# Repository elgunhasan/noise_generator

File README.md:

| Band | S-meter | μV |
| ------ | ------ |------ |
| 10 meter | 8 | 31 |
| 12 meter | 8 | 31 |
| 15 meter | 9 | 61 |
| 17 meter | 9 | 61 |
| 20 meter | 9+10 db | 190 |
| 30 meter | 9+20 db | 610 |
| 40 meter | 9+20 db | 610 |
| 80 meter | 9+20 db | 610 |
| 160 meter | 9+20 db | 610 |

You can change the resistor R1 with a potentiometer and find out at which value the strongest noise occurs.

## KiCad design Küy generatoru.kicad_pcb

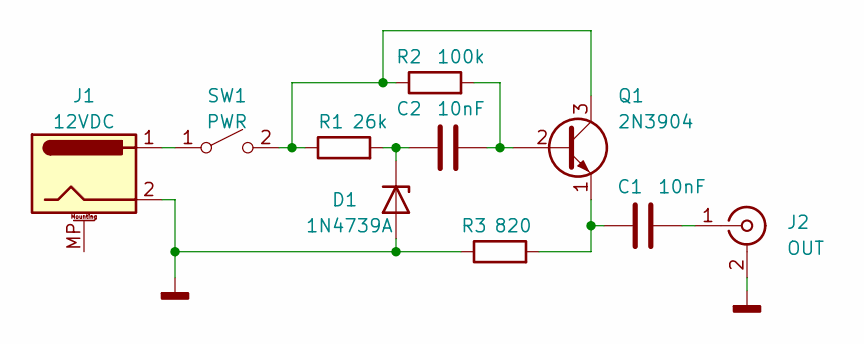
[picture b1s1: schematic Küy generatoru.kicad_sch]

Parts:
C1, C2: 10nF; C_Disc_D4.3mm_W1.9mm_P5.00mm
D1: 1N4739A; D_DO-41_SOD81_P10.16mm_Horizontal
J1: 12VDC; BarrelJack_GCT_DCJ200-10-A_Horizontal
J2: OUT; SMA_Amphenol_901-143_Horizontal
Q1: 2N3904; TO-92L_Inline_Wide
R1: 26k; R_Axial_DIN0207_L6.3mm_D2.5mm_P2.54mm_Vertical
R2: 100k; R_Axial_DIN0207_L6.3mm_D2.5mm_P2.54mm_Vertical
R3: 820; R_Axial_DIN0207_L6.3mm_D2.5mm_P2.54mm_Vertical
SW1: PWR; SW_CuK_OS102011MA1QN1_SPDT_Angled

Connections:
GNDD: D1.2 (A), J1.2, J2.2 (Ext), R3.1
unnamed: C2.2, D1.1 (K), R1.2
unnamed: C1.1, J2.1 (In)
unnamed: C2.1, Q1.2 (B), R2.2
unnamed: Q1.3 (C), R1.1, R2.1, SW1.2 (B)
unnamed: C1.2, Q1.1 (E), R3.2
unnamed: J1.1, SW1.1 (A)

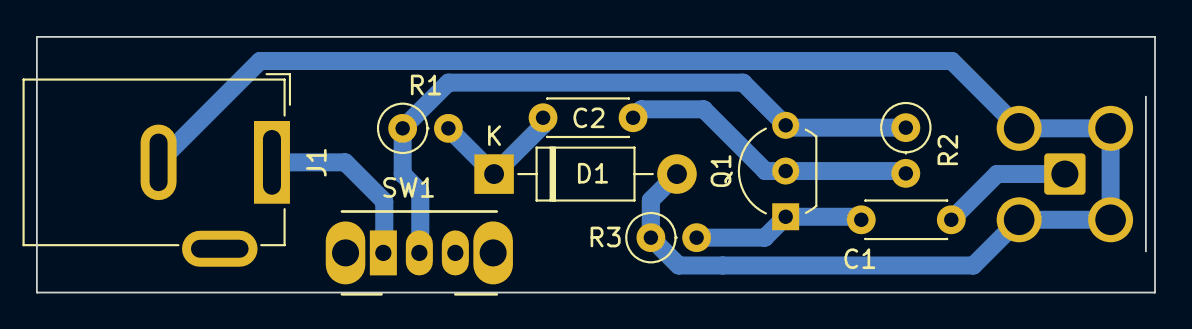
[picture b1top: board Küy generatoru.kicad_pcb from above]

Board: 2 copper layers, 62.1 x 14.2 mm, 10 parts (1 on the bottom side), 7 nets.
